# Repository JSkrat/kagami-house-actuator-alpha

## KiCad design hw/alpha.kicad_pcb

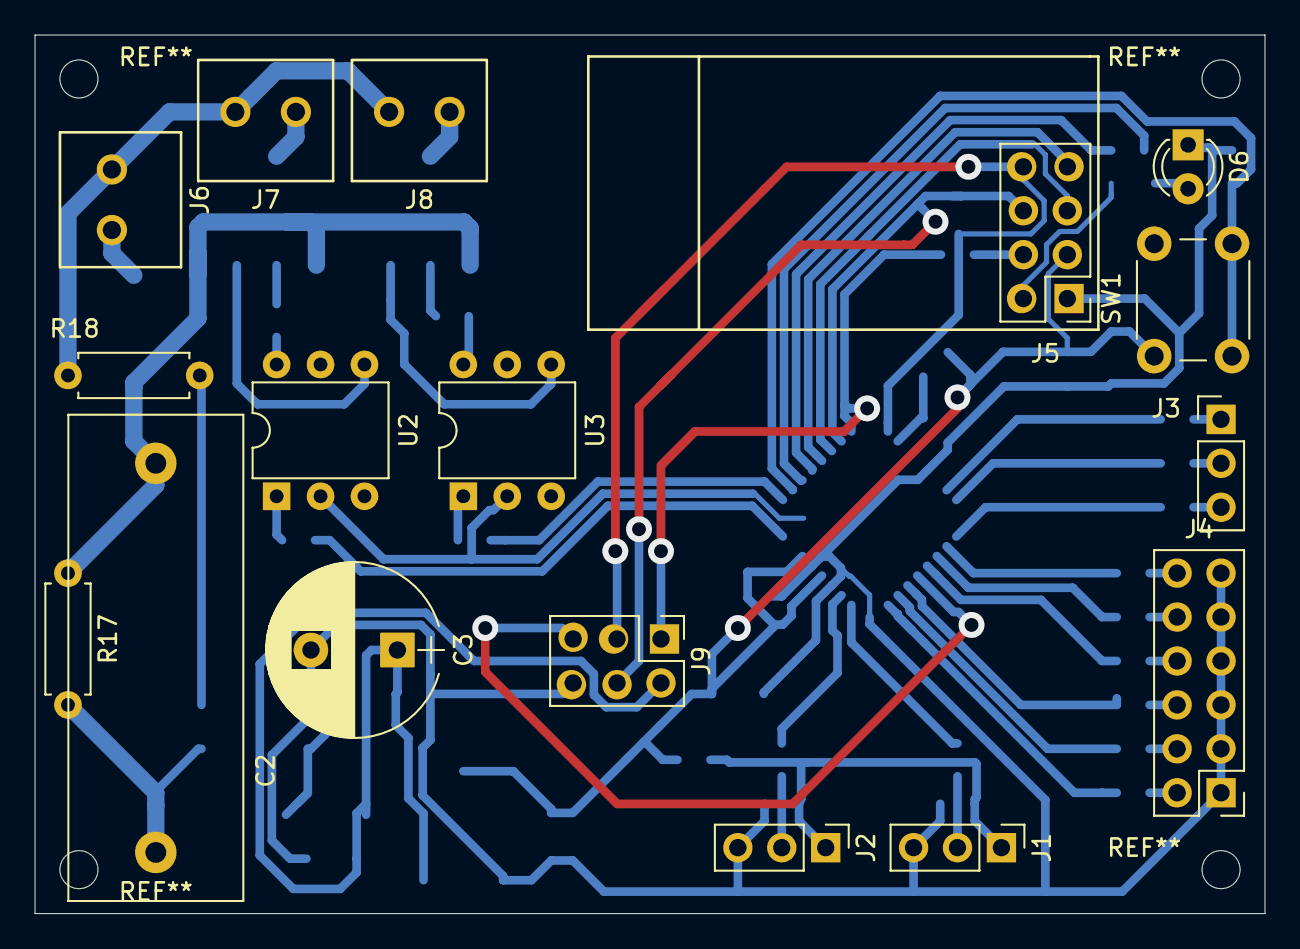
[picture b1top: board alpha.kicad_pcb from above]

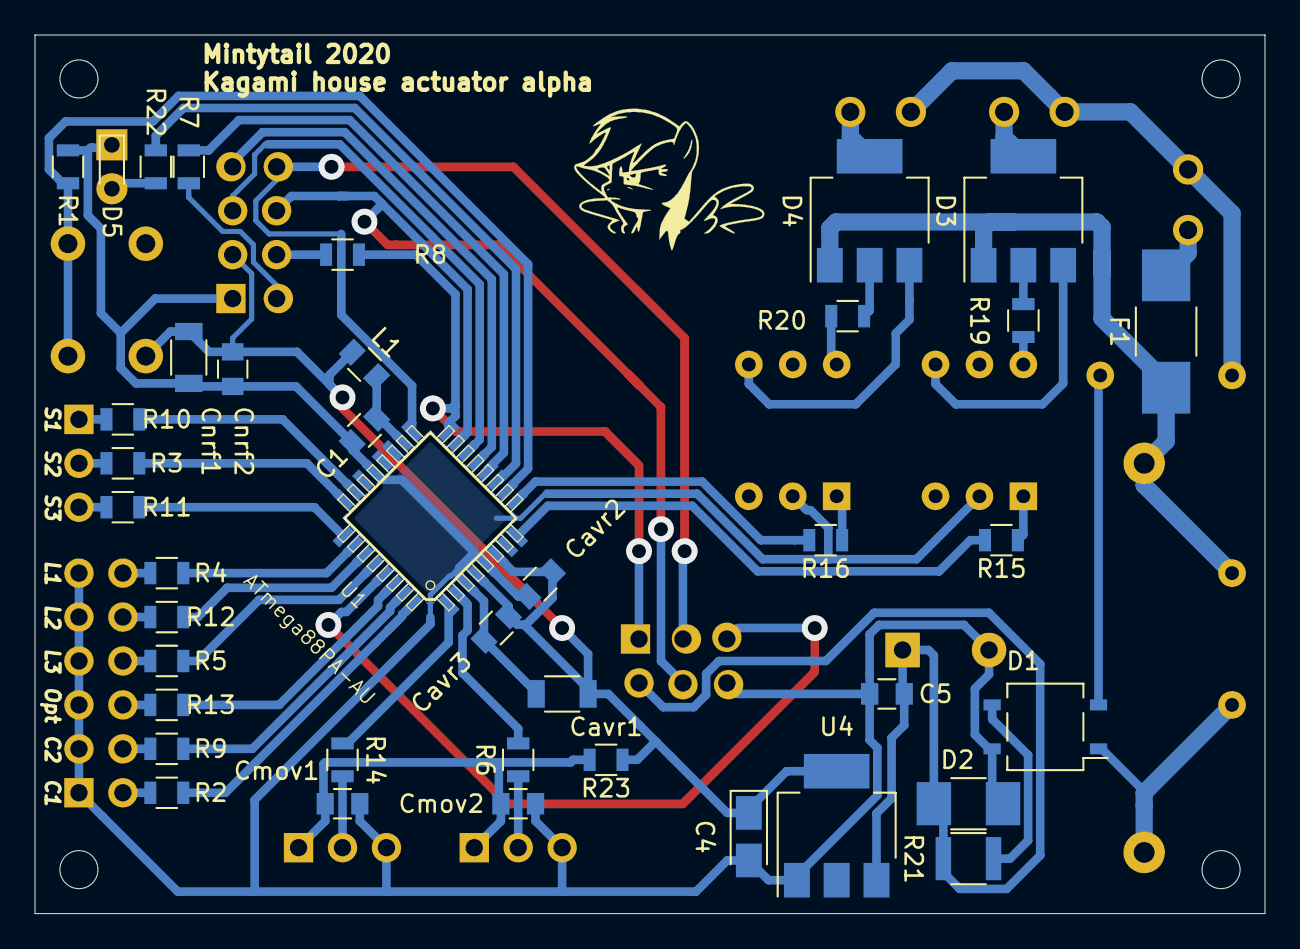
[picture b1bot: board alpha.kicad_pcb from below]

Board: 2 copper layers, 71.1 x 50.8 mm, 57 parts (40 on the bottom side), 55 nets.

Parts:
C1, C5: 100n; C_0805
C2: 1uF; C_Rect_L28.0mm_W10.0mm_P22.50mm_MKS4
C3: 1000uF; CP_Radial_D10.0mm_P5.00mm
C4: 22uf; CP_Tantalum_Case-A_EIA-3216-18_Reflow
Cavr1: 1u; C_1206
Cavr2, Cavr3: 100n; C_0805
Cmov1, Cmov2: 100n; C_0805
Cnrf1: 1u; C_1206
Cnrf2: 100n; C_0805
D1: MB6S; Diode_Bridge_TO-269AA
D2: 1SMA5918BT3G; C_1210_HandSoldering
D3, D4: Z0107MN; SOT-223
D5: LED; LED_0805
D6: LED; LED_D3.0mm
F1: 3A; Fuse_SMD_Schurter_OMT125
J1, J2: PIR sensor; Pin_Header_Straight_1x03_Pitch2.54mm
J3: Control sensors; Pin_Header_Straight_1x03_Pitch2.54mm
J4: LEDs; Pin_Header_Straight_2x06_Pitch2.54mm
J5: NRF24L01
J6, J7, J8: 15EDGVC-3.5-02P; 15EDGVC-3.5_2
J9: AVR-ISP-6; Pin_Header_Straight_2x03_Pitch2.54mm
L1: 10uH; C_0805
R1: 4k7; R_0805
R2, R3, R4, R5, R9, R10, R11, R12, R13, R22: 150; R_0805
R6, R7, R8, R14: 22; R_0805
R15, R16: 210; R_0805
R17: 510k; R_Axial_DIN0207_L6.3mm_D2.5mm_P7.62mm_Horizontal
R18: 47; R_Axial_DIN0207_L6.3mm_D2.5mm_P7.62mm_Horizontal
R19, R20: 180; R_0805
R21: 100; R_1210
R23: 0; R_0805
SW1: advertisement mode; SW_PUSH_6mm_h4.3mm
U1: ATmega88PA-AU; atmega8-TQFP32-08
U2, U3: MOC3043M; DIP-6_W7.62mm
U4: AMS1117-3.3; SOT-223-3_TabPin2

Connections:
/3v3: C4.1, Cavr1.1, Cavr2.1, Cavr3.1, Cnrf1.1, Cnrf2.1, J5.2, L1.1, R23.1, SW1.2, U1.4, U1.6, U4.2
/5v1: C3.1, C5.1, D2.1, J9.2, R21.1, U4.3
/220_L: C2.1, D3.1, D4.1, F1.1, R17.1
/220_N: J6.2, J7.1, J8.1, R18.2
/220_out_1: D3.2, D3.4, J7.2, R19.1
/220_out_2: D4.2, D4.4, J8.2, R20.1
/L1: J4.12, R4.1
/L2: J4.10, R12.1
/L3: J4.8, R5.1
/S1: J3.1, R10.1
/S2: J3.2, R3.1
/S3: J3.3, R11.1
/adv_on: R1.1, SW1.1, U1.10
/avr_miso: J9.1, R8.2, U1.16
/avr_mosi: J5.6, J9.4, U1.15
/avr_rst: J9.5, U1.29
/avr_sck: J5.5, J9.3, U1.17
/ch1: J4.2, R2.1
/ch2: J4.4, R9.1
/gnd: C1.1, C3.2, C4.2, C5.2, Cavr1.2, Cavr2.2, Cavr3.2, Cmov1.2, Cmov2.2, Cnrf1.2, Cnrf2.2, D1.4, D2.2, D5.1, D6.1, J1.3, J2.3, J4.1, J4.3, J4.5, J4.7, J4.9, J4.11, J5.1, J9.6, R1.2, U1.3, U1.5, U1.21, U2.2, U3.2, U4.1
/mov_output_1: J1.2, R14.1
/mov_output_2: J2.2, R6.1
/nrf_ce: J5.3, U1.14
/nrf_cs: J5.4, U1.13
/nrf_irq: J5.8, R7.1
/nrf_miso: J5.7, R8.1
/opt: J4.6, R13.1
unnamed: C1.2, L1.2, U1.18
unnamed: C2.2, D1.1, R17.2
unnamed: Cmov1.1, Cmov2.1, J1.1, J2.1, R23.2
unnamed: D1.2, R18.1
unnamed: D1.3, R21.2
unnamed: D3.3, U2.4
unnamed: D4.3, U3.4
unnamed: D5.2, D6.2, R22.2
unnamed: F1.2, J6.1
unnamed: R2.2, U1.32
unnamed: R3.2, U1.24
unnamed: R4.2, U1.26
unnamed: R5.2, U1.28
unnamed: R6.2, U1.2
unnamed: R7.2, U1.12
unnamed: R9.2, U1.31
unnamed: R10.2, U1.23
unnamed: R11.2, U1.25
unnamed: R12.2, U1.27
unnamed: R13.2, U1.30
unnamed: R14.2, U1.1
unnamed: R15.1, U2.1
unnamed: R15.2, U1.8
unnamed: R16.1, U3.1
unnamed: R16.2, U1.9
unnamed: R19.2, U2.6
unnamed: R20.2, U3.6
unnamed: R22.1, U1.11

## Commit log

2022-07-09 adapt to new protocol format
2022-07-09 add hw
2022-07-11 use built-in advertisement
